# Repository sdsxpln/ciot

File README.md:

## LICENSE
This project is provided under the MIT Licence unless an alternative licence is provided in source.

## LIBRARIES

- [X-CUBE-MEMS1](http://www.st.com/ja/embedded-software/x-cube-mems1.html)

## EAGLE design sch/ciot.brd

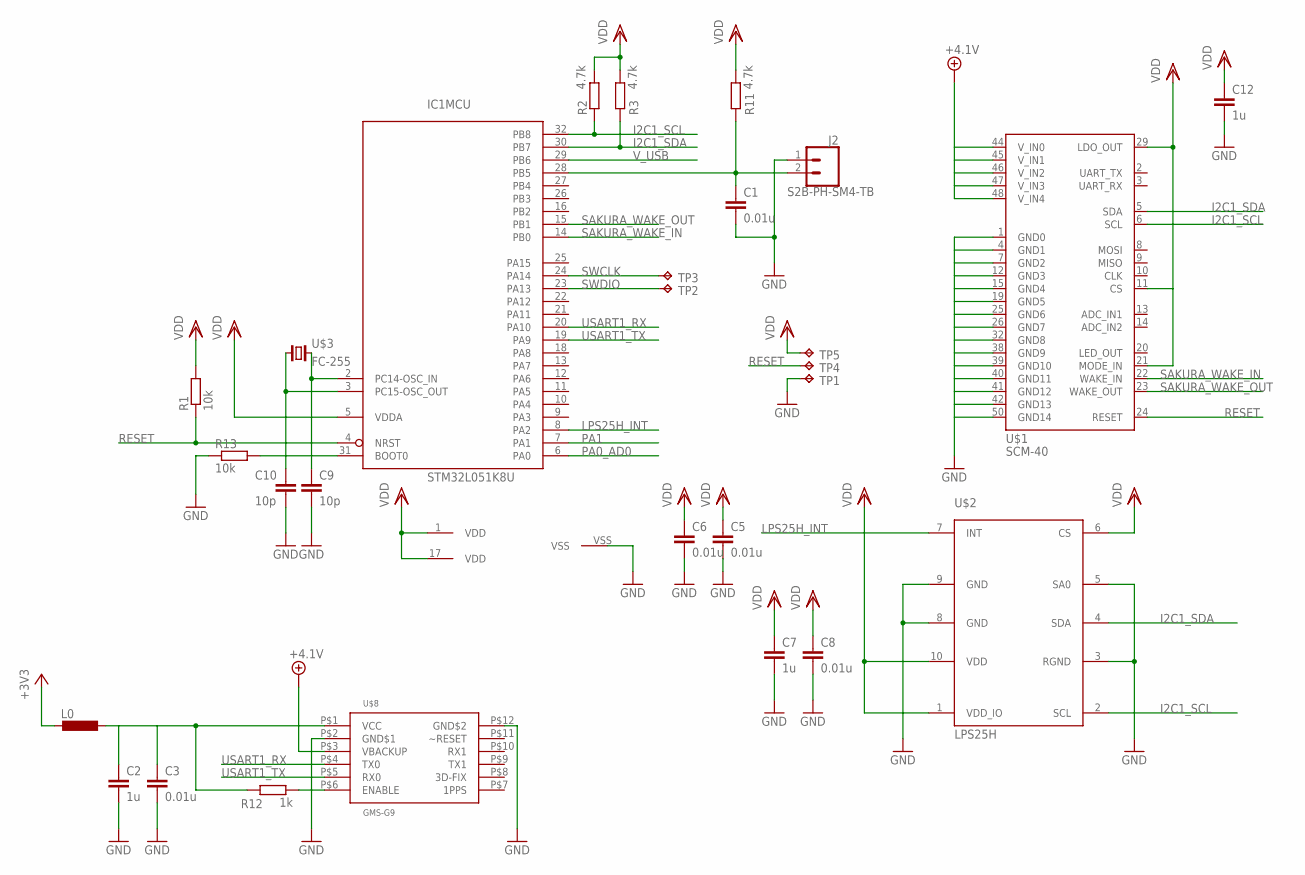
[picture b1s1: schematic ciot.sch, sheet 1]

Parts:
C1, C3, C5, C6, C8: 0.01u; C0603K
C2, C7, C12: 1u; C0603K
C9, C10: 10p; C0603K
IC1: STM32L051K8U; UFQFPN32
J2: S2B-PH-SM4-TB; JST-2-SMD
L0: L-EUL2012C; L2012C
R1, R13: 10k; R0603
R2, R3, R11: 4.7k; R0603
R12: 1k; R0603
TP1, TP2, TP3, TP4, TP5: TPB1,27; B1,27
U$1: SCM-40; SCM-DF40-50DS
U$2: LPS25H
U$3: FC-255
U$8: GMS-G9

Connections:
+3V3: L0.2; also elsewhere on the board
+4.1V: U$1.44 (V_IN0), U$1.45 (V_IN1), U$1.46 (V_IN2), U$1.47 (V_IN3), U$1.48 (V_IN4), U$8.P$3 (VBACKUP); also elsewhere on the board
GND: C1.2, C2.2, C3.2, C5.2, C6.2, C7.2, C8.2, C9.2, C10.2, C12.2, IC1.VSS, J2.1 (2), R13.1, TP1.TP, U$1.1 (GND0), U$1.4 (GND1), U$1.7 (GND2), U$1.12 (GND3), U$1.15 (GND4), U$1.19 (GND5), U$1.25 (GND6), U$1.26 (GND7), U$1.32 (GND8), U$1.38 (GND9), U$1.39 (GND10), U$1.40 (GND11), U$1.41 (GND12), U$1.42 (GND13), U$1.50 (GND14), U$2.3 (RGND), U$2.5 (SA0), U$2.8 (GND), U$2.9 (GND), U$8.P$2 (GND$1), U$8.P$12 (GND$2); also elsewhere on the board
I2C1_SCL: IC1.32 (PB8), R2.1, U$1.6 (SCL), U$2.2 (SCL)
I2C1_SDA: IC1.30 (PB7), R3.1, U$1.5 (SDA), U$2.4 (SDA)
LPS25H_INT: IC1.8 (PA2), U$2.7 (INT)
unnamed: IC1.31 (BOOT0), R13.2
unnamed: C2.1, C3.1, L0.1, R12.1, U$8.P$1 (VCC)
unnamed: C1.1, IC1.28 (PB5), J2.2 (1), R11.1
unnamed: C10.1, IC1.3 (PC15-OSC_OUT), U$3.1
unnamed: C9.1, IC1.2 (PC14-OSC_IN), U$3.2
unnamed: R12.2, U$8.P$6 (ENABLE)
PA0_AD0: IC1.6 (PA0); also elsewhere on the board
PA1: IC1.7 (PA1); also elsewhere on the board
RESET: IC1.4 (NRST), R1.1, TP4.TP, U$1.24 (RESET)
SAKURA_WAKE_IN: IC1.14 (PB0), U$1.22 (WAKE_IN)
SAKURA_WAKE_OUT: IC1.15 (PB1), U$1.23 (WAKE_OUT)
SWCLK: IC1.24 (PA14), TP3.TP
SWDIO: IC1.23 (PA13), TP2.TP
USART1_RX: IC1.20 (PA10), U$8.P$4 (TX0)
USART1_TX: IC1.19 (PA9), U$8.P$5 (RX0)
VDD: C5.1, C6.1, C7.1, C8.1, C12.1, IC1.1 (VDD), IC1.5 (VDDA), IC1.17 (VDD), R1.2, R2.2, R3.2, R11.2, TP5.TP, U$1.11 (CS), U$1.21 (MODE_IN), U$1.29 (LDO_OUT), U$2.1 (VDD_IO), U$2.6 (CS), U$2.10 (VDD)
V_USB: IC1.29 (PB6); also elsewhere on the board

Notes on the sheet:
LPS25H

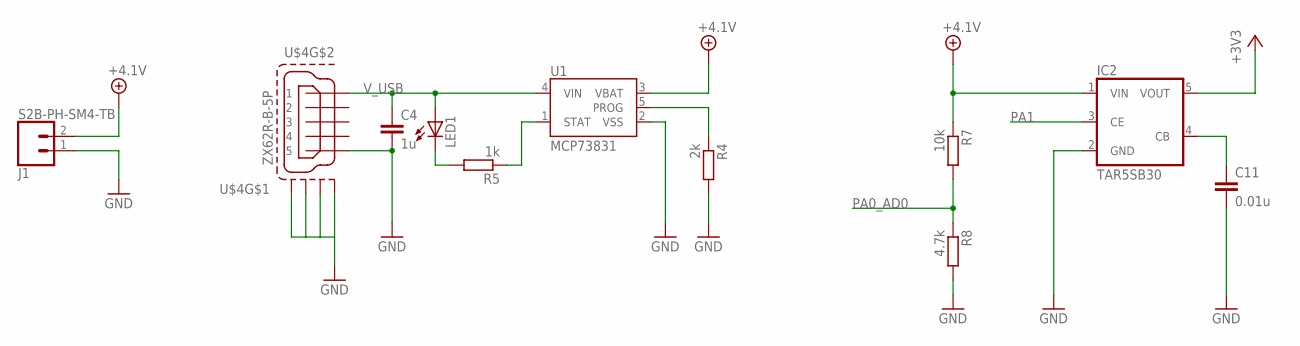
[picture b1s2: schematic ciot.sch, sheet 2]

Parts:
C4: 1u; C0603K
C11: 0.01u; C0603K
IC2: TAR5SB30; SOT25
J1: S2B-PH-SM4-TB; JST-2-SMD
LED1: LEDCHIPLED_0603; CHIPLED_0603
R4: 2k; R0603
R5: 1k; R0603
R7: 10k; R0603
R8: 4.7k; R0603
U1: MCP73831; SOT23-5
U$4: ZX62R-B-5P

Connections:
+3V3: IC2.5 (VOUT); also elsewhere on the board
+4.1V: IC2.1 (VIN), J1.2 (1), R7.1, U1.3 (VBAT); also elsewhere on the board
GND: C4.2, C11.2, IC2.2 (GND), J1.1 (2), R4.2, R8.2, U1.2 (VSS), U$4.5, U$4.M1 (S1), U$4.M2 (S2), U$4.M3 (S3), U$4.M4 (S4); also elsewhere on the board
unnamed: C11.1, IC2.4 (CB)
unnamed: LED1.C, R5.2
unnamed: R5.1, U1.1 (STAT)
unnamed: R4.1, U1.5 (PROG)
PA0_AD0: R7.2, R8.1; also elsewhere on the board
PA1: IC2.3 (CE); also elsewhere on the board
V_USB: C4.1, LED1.A, U1.4 (VIN), U$4.1; also elsewhere on the board

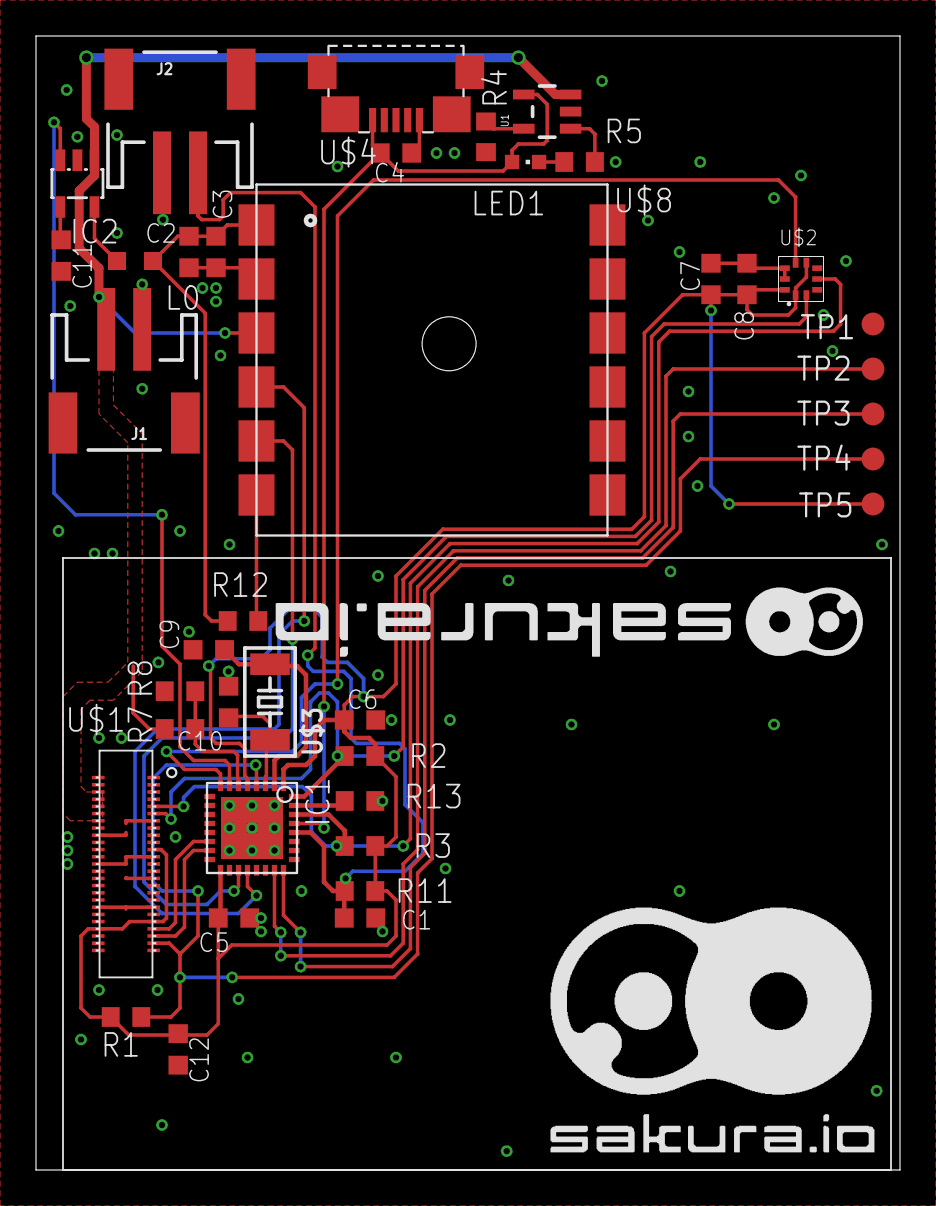
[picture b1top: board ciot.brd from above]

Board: 2 copper layers, 48.0 x 63.0 mm, 40 parts (0 on the bottom side), 27 nets.

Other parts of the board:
U$5: LOGO-SAKURAIO-3

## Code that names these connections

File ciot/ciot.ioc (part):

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Mcu.Name=STM32L051K(6-8)Ux
Mcu.Package=UFQFPN32
Mcu.UserName=STM32L051K8Ux
PA0.GPIOParameters=GPIO_Label
PA0.GPIO_Label=AD_BATTERY
PA0.Mode=IN0
PA0.Signal=ADC_IN0
PA1.GPIOParameters=GPIO_Label
PA1.GPIO_Label=GPS_ENABLE
PA1.Signal=GPIO_Output
PA10.Mode=Asynchronous
PA10.Signal=USART1_RX
PA13.Mode=Serial_Wire
PA13.Signal=SYS_SWDIO
PA14.Mode=Serial_Wire
PA14.Signal=SYS_SWCLK
PA9.Mode=Asynchronous
PA9.Signal=USART1_TX
PB0.GPIOParameters=GPIO_Label
PB0.GPIO_Label=SAKURA_WAKE_IN
PB0.Signal=GPIO_Output
PB1.GPIOParameters=GPIO_PuPd,GPIO_Label
PB1.GPIO_Label=SAKURA_WAKE_OUT
PB1.GPIO_PuPd=GPIO_PULLDOWN
PB1.Signal=GPIO_Input
PB5.GPIOParameters=GPIO_Label,GPIO_ModeDefaultEXTI
PB5.GPIO_Label=REED_SWITCH
PB5.GPIO_ModeDefaultEXTI=GPIO_MODE_IT_FALLING
PB5.Signal=GPXTI5
PB6.GPIOParameters=GPIO_PuPd,GPIO_Label,GPIO_ModeDefaultEXTI
PB6.GPIO_Label=V_USB
PB6.GPIO_ModeDefaultEXTI=GPIO_MODE_IT_RISING
PB6.GPIO_PuPd=GPIO_PULLDOWN
PB6.Signal=GPXTI6
PB7.GPIOParameters=GPIO_PuPdOD,GPIO_FM7
PB7.GPIO_FM7=__NULL
PB7.GPIO_PuPdOD=GPIO_NOPULL
PB7.Mode=I2C
PB7.Signal=I2C1_SDA
PB8.GPIOParameters=GPIO_PuPdOD,GPIO_FM8
PB8.GPIO_FM8=__NULL
PB8.GPIO_PuPdOD=GPIO_NOPULL
PB8.Mode=I2C
PB8.Signal=I2C1_SCL
PC14-OSC32_IN.Mode=LSE-External-Oscillator
PC14-OSC32_IN.Signal=RCC_OSC32_IN
PC15-OSC32_OUT.Mode=LSE-External-Oscillator
PC15-OSC32_OUT.Signal=RCC_OSC32_OUT
RCC.SYSCLKFreq_VALUE=32000000
RCC.SYSCLKSource=RCC_SYSCLKSOURCE_PLLCLK
board=ciot

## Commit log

2017-05-06 Add a CubeMX project
2017-05-06 Add eagle project
2017-08-17 update CubeMX
2017-08-17 Update EAGLE files
2017-08-18 Add README.md
2017-08-18 Get humidity and temperature
2017-08-18 fix warning
2017-08-20 Get latitude and longitude from GPS
2017-08-20 Enable ADC
2017-08-21 Communicate with sakura.io module
2017-08-21 Improve accuracy of air pressure sensor
2017-08-22 Fix CubeMX settings
2017-08-23 Use RTC and LPTIM
2017-08-24 Use queue for transmitting data by sakura.io
2017-08-24 bug fix
2017-08-24 Add status channel
2017-08-30 GPSから日時を取得
2017-09-09 Supoort GNRMC
2017-09-16 Low power mode
2017-09-18 power down mode

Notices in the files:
parts and their libraries:
SparkFun-Connectors: Licensing: Creative Commons ShareAlike 4.0 International - https://creativecommons.org/licenses/by-sa/4.0
SparkFun-PowerIC: Licensing: CC v3.0 Share-Alike You are welcome to use this library for commercial purposes.
